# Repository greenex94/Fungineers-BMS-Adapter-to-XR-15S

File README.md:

# Fungineers-BMS-Adapter-to-XR-15S
Simple adapter board to convert 26-pin XR stock 15S battery BMS connector to JST PH connector pigtails for the Fungineers BMS board.

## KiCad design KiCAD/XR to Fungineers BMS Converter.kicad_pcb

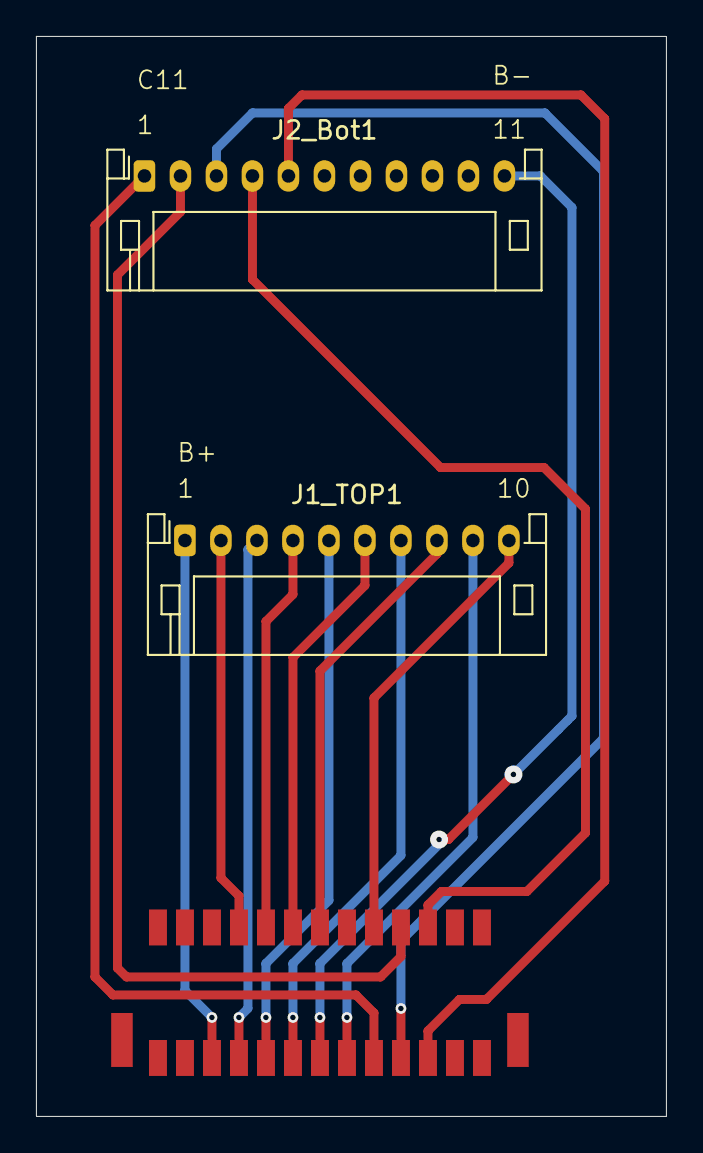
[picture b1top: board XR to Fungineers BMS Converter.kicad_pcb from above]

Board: 2 copper layers, 35.0 x 60.0 mm, 3 parts (0 on the bottom side), 16 nets.

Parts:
J1_TOP1: Conn_01x10; JST_PH_S10B-PH-K_1x10_P2.00mm_Horizontal
J2_Bot1: Conn_01x10; JST_PH_S11B-PH-K_1x11_P2.00mm_Horizontal
J3: Conn_02x10_Odd_Even; JST_ZPD_26

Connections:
bms_01: J1_TOP1.1, J3.21
bms_02: J1_TOP1.2, J3.20
bms_03: J1_TOP1.3, J3.19
bms_04: J1_TOP1.4, J3.18
bms_05: J1_TOP1.5, J3.17
bms_06: J1_TOP1.6, J3.16
bms_07: J1_TOP1.7, J3.15
bms_08: J1_TOP1.8, J3.14
bms_09: J1_TOP1.9, J3.11
bms_10: J1_TOP1.10, J3.10
bms_11: J2_Bot1.1, J3.9
bms_12: J2_Bot1.2, J3.8
bms_13: J2_Bot1.3, J3.7
bms_14: J2_Bot1.4, J3.6
bms_15: J2_Bot1.5, J3.5
bms_16: J2_Bot1.11, J3.13

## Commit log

2024-04-03 Create 1
